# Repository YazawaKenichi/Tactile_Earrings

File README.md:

# Tactile_Earrings 

タクトスイッチのピアス ( Tactile Earrings ) 

[@shacho_tech](https://twitter.com/@shacho_tech) によって提案されたタクトスイッチのピアスの基板

# Development Software Versions
Application: KiCad x64 on x64

Version: 7.0.6, release build

Libraries:
	wxWidgets 3.2.2
	FreeType 2.12.1
	HarfBuzz 6.0.0
	FontConfig 2.14.1
	libcurl/7.88.1-DEV Schannel zlib/1.2.13

Platform: Windows 10 (build 19045), 64-bit edition, 64 bit, Little endian, wxMSW

Build Info:
	Date: Jul  6 2023 04:56:45
	wxWidgets: 3.2.2 (wchar_t,wx containers)
	Boost: 1.81.0
	OCC: 7.6.3
	Curl: 7.88.1-DEV
	ngspice: 40
	Compiler: Visual C++ 1936 without C++ ABI

Build settings:
	KICAD_SPICE=ON

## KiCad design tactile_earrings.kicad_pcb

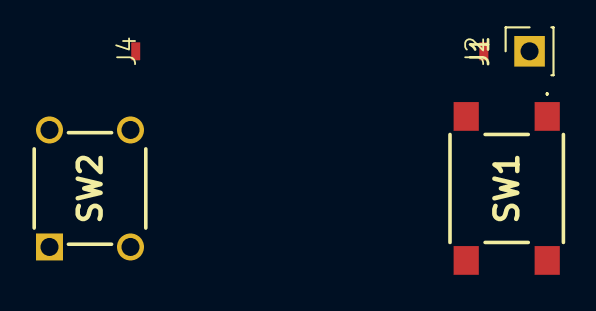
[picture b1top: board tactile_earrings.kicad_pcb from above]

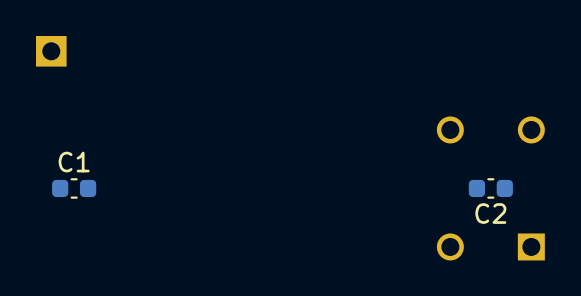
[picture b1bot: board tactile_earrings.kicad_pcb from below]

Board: 2 copper layers, 7 parts (2 on the bottom side), 3 nets, no tracks yet.

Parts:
C1, C2: 0.1u; C_0603_1608Metric
J1: Conn_01x01_Pin; PinSocket_1x01_P2.54mm_Vertical
J2, J4: Conn_01x01_Pin; Exposed_Pad
SW1: SW_MEC_5E; B3FS1050
SW2: SW_MEC_5E; DTS63NV

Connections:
GND: C1.2, C2.2, J2.1, J4.1, SW1.3 (K), SW1.4 (A), SW2.3 (K), SW2.4 (A)
unnamed: C1.1, J1.1, SW1.1, SW1.2
unnamed: C2.1, SW2.1, SW2.2

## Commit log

2023-08-22 回路図作った。パターンは製作中
2023-08-22 れどめにアプリケーションのバージョンを記載
2023-08-22 一時保存ファイル的なものを削除した
